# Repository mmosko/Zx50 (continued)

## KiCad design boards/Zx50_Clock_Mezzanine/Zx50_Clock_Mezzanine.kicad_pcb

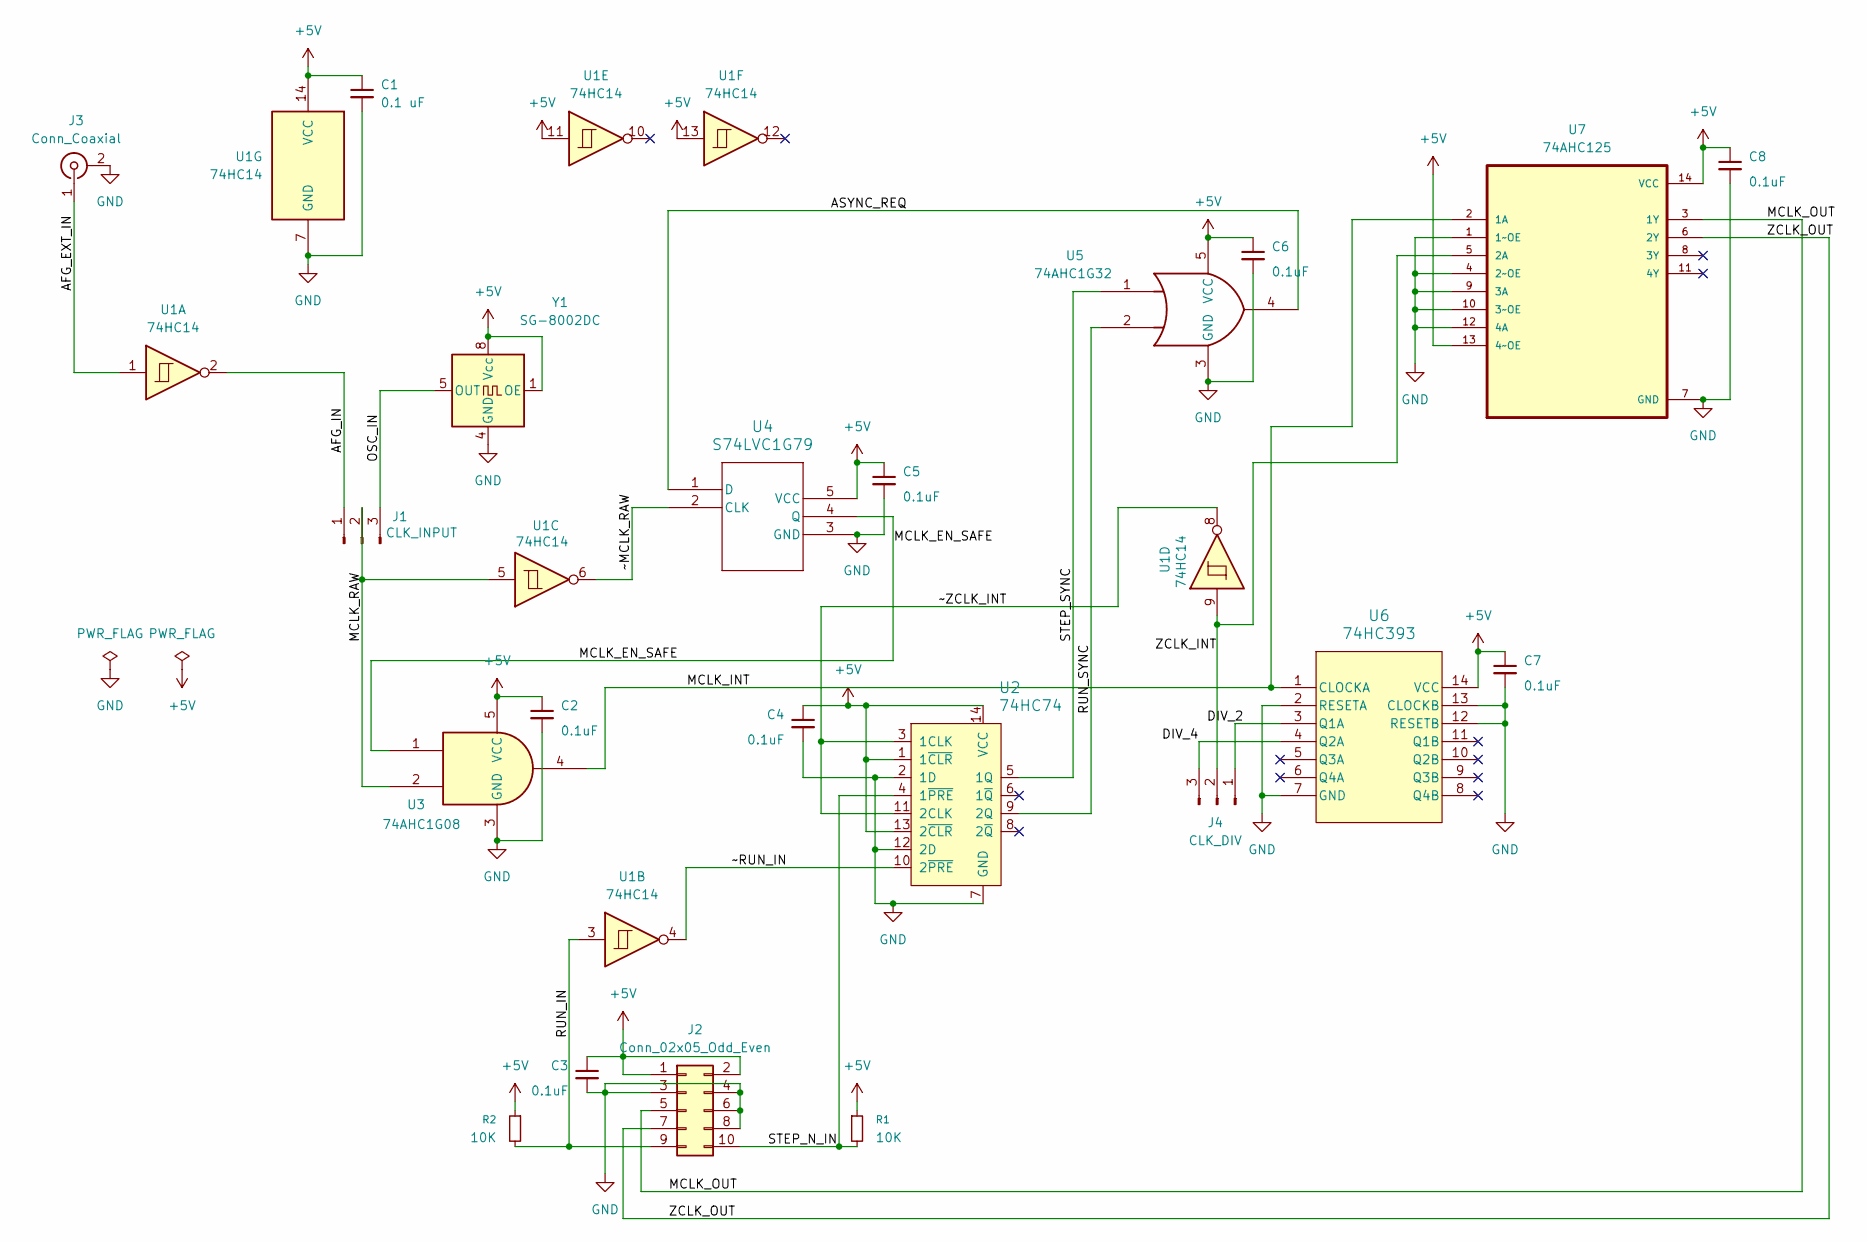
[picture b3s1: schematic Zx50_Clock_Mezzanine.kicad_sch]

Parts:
C1: 0.1 uF; C_0805_2012Metric_Pad1.18x1.45mm_HandSolder; DigiKey_PN 311-1140-1-ND
C2, C3, C4, C5, C6, C7, C8: 0.1uF; C_0805_2012Metric_Pad1.18x1.45mm_HandSolder; DigiKey_PN 311-1140-1-ND
J1: CLK_INPUT; PinHeader_1x03_P2.54mm_Vertical; DigiKey_PN 732-5316-ND
J2: Conn_02x05_Odd_Even; PinHeader_2x05_P2.54mm_Vertical; DigiKey_PN 2057-PH2RA-10-UA-ND
J3: Conn_Coaxial; BNC_Amphenol_B6252HB-NPP3G-50_Horizontal; DigiKey_PN ARF1178-ND
J4: CLK_DIV; PinHeader_1x03_P2.54mm_Vertical; DigiKey_PN 732-5316-ND
R1, R2: 10K; R_0805_2012Metric_Pad1.20x1.40mm_HandSolder; DigiKey_PN 311-10.0KCRCT-ND
U1: 74HC14; SOIC-14_3.9x8.7mm_P1.27mm; DigiKey_PN MC74HC14ADR2GOSCT-ND
U2: 74HC74; SOIC-14_3.9x8.7mm_P1.27mm; MPN SN74HC74N; Digi-Key_PN 296-1602-5-ND
U3: 74AHC1G08; SOT-23-5_HandSoldering; DigiKey_PN 296-1091-1-ND
U4: S74LVC1G79; SOT-23-5_HandSoldering; DigiKey_PN 296-9849-1-ND
U5: 74AHC1G32; SOT-23-5_HandSoldering; DigiKey_PN 296-1093-1-ND
U6: 74HC393; SOIC-14_3.9x8.7mm_P1.27mm; DigiKey_PN 296-8317-5-ND
U7: 74AHC125; SOIC-14_3.9x8.7mm_P1.27mm; DigiKey_PN 296-4530-1-ND
Y1: SG-8002DC; DIP-8_W7.62mm_Socket; DigiKey_PN 17-2485264-1-ND

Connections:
+5V: C1.1, C2.1, C3.1, C4.1, C5.1, C6.1, C7.1, C8.1, J2.1, J2.2, R1.1, R2.1, U1.11, U1.13, U1.14 (VCC), U2.1 (1~CLR), U2.13 (2~CLR), U2.14 (VCC), U3.5 (VCC), U4.5 (VCC), U5.5 (VCC), U6.14 (VCC), U7.13 (4~OE), U7.14 (VCC), Y1.1 (OE), Y1.8 (Vcc)
/AFG_EXT_IN: J3.1 (In), U1.1
/AFG_IN: J1.1, U1.2
/ASYNC_REQ: U4.1 (D), U5.4
/DIV_2: J4.1, U6.3 (Q1A)
/DIV_4: J4.3, U6.4 (Q2A)
/MCLK_EN_SAFE: U3.1, U4.4 (Q)
/MCLK_INT: U3.4, U6.1 (CLOCKA), U7.2 (1A)
/MCLK_OUT: J2.5, U7.3 (1Y)
/MCLK_RAW: J1.2, U1.5, U3.2
/OSC_IN: J1.3, Y1.5 (OUT)
/RUN_IN: J2.9, R2.2, U1.3
/RUN_SYNC: U2.9 (2Q), U5.2
/STEP_N_IN: J2.10, R1.2, U2.4 (1~PRE)
/STEP_SYNC: U2.5 (1Q), U5.1
/ZCLK_INT: J4.2, U1.9, U7.5 (2A)
/ZCLK_OUT: J2.7, U7.6 (2Y)
/~MCLK_RAW: U1.6, U4.2 (CLK)
/~RUN_IN: U1.4, U2.10 (2~PRE)
/~ZCLK_INT: U1.8, U2.3 (1CLK), U2.11 (2CLK)
GND: C1.2, C2.2, C3.2, C4.2, C5.2, C6.2, C7.2, C8.2, J2.3, J2.4, J2.6, J2.8, J3.2 (Ext), U1.7 (GND), U2.2 (1D), U2.7 (GND), U2.12 (2D), U3.3 (GND), U4.3 (GND), U5.3 (GND), U6.2 (RESETA), U6.7 (GND), U6.12 (RESETB), U6.13 (CLOCKB), U7.1 (1~OE), U7.4 (2~OE), U7.7 (GND), U7.9 (3A), U7.10 (3~OE), U7.12 (4A), Y1.4 (GND)

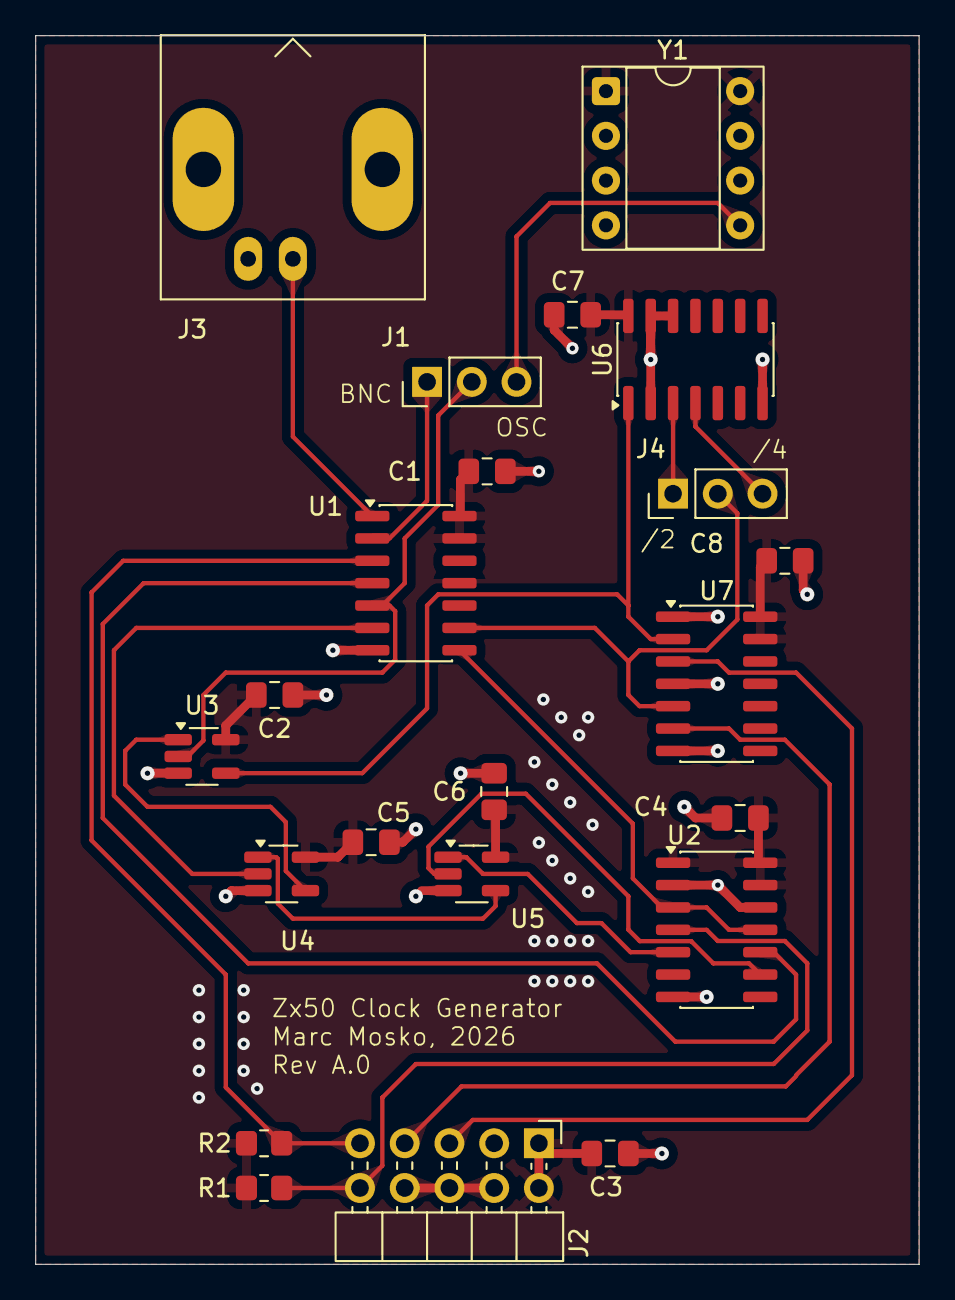
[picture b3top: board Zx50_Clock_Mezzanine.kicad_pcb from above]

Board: 2 copper layers, 50.2 x 69.8 mm, 22 parts (0 on the bottom side), 21 nets.

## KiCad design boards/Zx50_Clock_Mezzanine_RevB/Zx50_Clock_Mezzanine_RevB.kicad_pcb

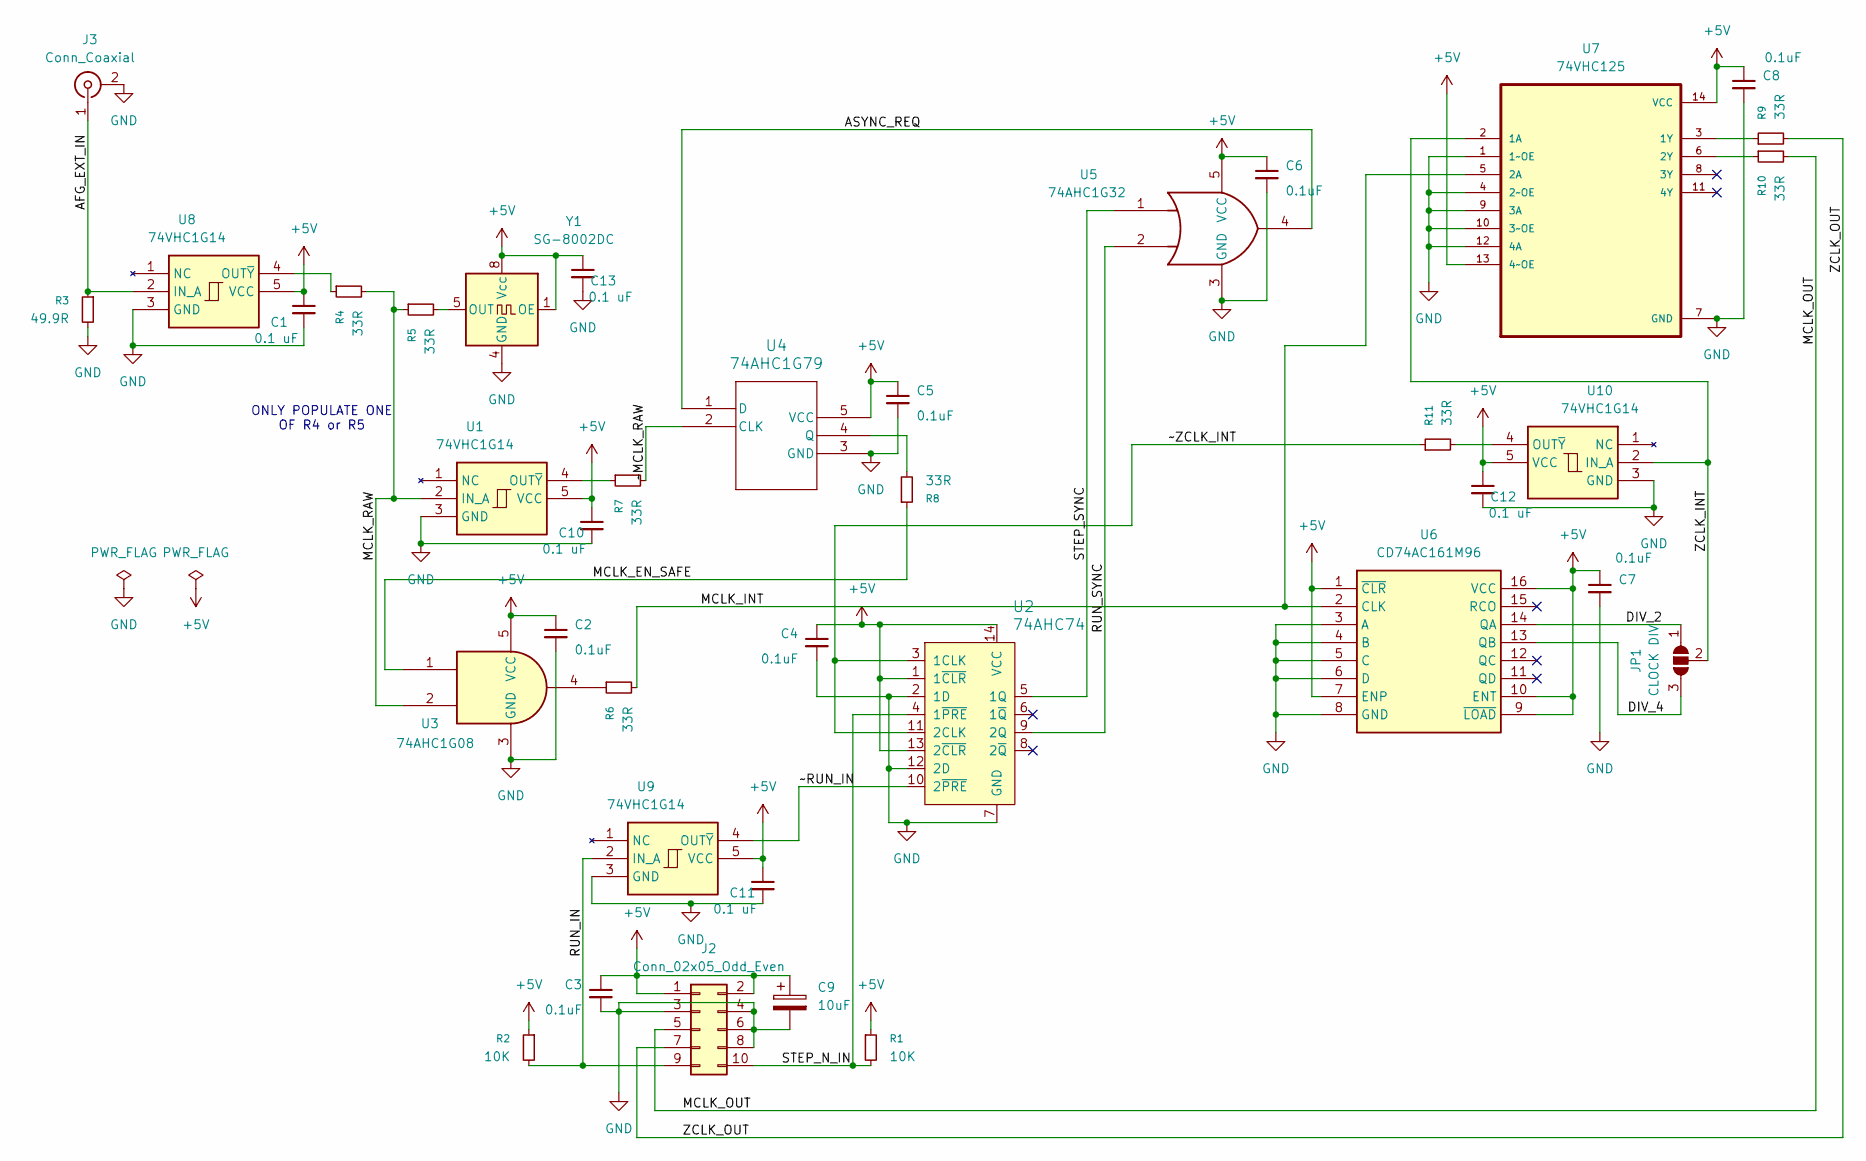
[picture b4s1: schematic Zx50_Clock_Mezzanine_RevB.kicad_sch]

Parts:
C1, C10, C11, C12, C13: 0.1 uF; C_0805_2012Metric_Pad1.18x1.45mm_HandSolder; DigiKey_PN 311-1140-1-ND
C2, C3, C4, C5, C6, C7, C8: 0.1uF; C_0805_2012Metric_Pad1.18x1.45mm_HandSolder; DigiKey_PN 311-1140-1-ND
C9: 10uF; CP_Radial_Tantal_D5.0mm_P2.50mm; Mouser_PN 80-T350E106K025; DigiKey_PN 399-1418-ND
J2: Conn_02x05_Odd_Even; PinHeader_2x05_P2.54mm_Vertical; DigiKey_PN 2057-PH2RA-10-UA-ND
J3: Conn_Coaxial; BNC_Amphenol_B6252HB-NPP3G-50_Horizontal; DigiKey_PN ARF1178-ND
JP1: CLOCK DIV; SolderJumper-3_P1.3mm_Open_RoundedPad1.0x1.5mm
R1, R2: 10K; R_0805_2012Metric_Pad1.20x1.40mm_HandSolder; DigiKey_PN 311-10.0KCRCT-ND
R3: 49.9R; R_0805_2012Metric_Pad1.20x1.40mm_HandSolder; DigiKey_PN 311-49.9KCRCT-ND
R4, R5, R6, R7, R8, R9, R10, R11: 33R; R_0805_2012Metric_Pad1.20x1.40mm_HandSolder; DigiKey_PN 311-33.0CRCT-ND
U1, U8, U9, U10: 74VHC1G14; SOT-23-5_HandSoldering; Mouser Part Number 863-MC74VHC1G14DBVTG
U2: 74AHC74; SOIC-14_3.9x8.7mm_P1.27mm; MPN SN74AHC74DR; Digi-Key_PN 296-1105-1-ND
U3: 74AHC1G08; SOT-23-5_HandSoldering; DigiKey_PN 296-1091-1-ND
U4: 74AHC1G79; SOT-23-5_HandSoldering; DigiKey_PN 1727-6765-1-ND
U5: 74AHC1G32; SOT-23-5_HandSoldering; DigiKey_PN 296-1093-1-ND
U6: CD74AC161M96; SOIC-16_3.9x9.9mm_P1.27mm; Mouser Part Number 595-CD74AC161M96
U7: 74VHC125; SOIC-14_3.9x8.7mm_P1.27mm; DigiKey_PN MC74VHC125DR2GOSCT-ND
Y1: SG-8002DC; DIP-8_W7.62mm_Socket; DigiKey_PN 17-2485264-1-ND

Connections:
+5V: C1.1, C2.1, C3.1, C4.1, C5.1, C6.1, C7.1, C8.1, C9.1, C10.1, C11.1, C12.1, C13.1, J2.1, J2.2, R1.1, R2.1, U1.5 (VCC), U2.1 (1~CLR), U2.13 (2~CLR), U2.14 (VCC), U3.5 (VCC), U4.5 (VCC), U5.5 (VCC), U6.1 (~CLR), U6.7 (ENP), U6.9 (~LOAD), U6.10 (ENT), U6.16 (VCC), U7.13 (4~OE), U7.14 (VCC), U8.5 (VCC), U9.5 (VCC), U10.5 (VCC), Y1.1 (OE), Y1.8 (Vcc)
/AFG_EXT_IN: J3.1 (In), R3.1, U8.2 (IN_A)
/ASYNC_REQ: U4.1 (D), U5.4
/DIV_2: JP1.1 (A), U6.14 (QA)
/DIV_4: JP1.3 (B), U6.13 (QB)
/MCLK_EN_SAFE: R8.1, U3.1
/MCLK_INT: R6.2, U6.2 (CLK), U7.5 (2A)
/MCLK_OUT: J2.5, R10.2
/MCLK_RAW: R4.2, R5.1, U1.2 (IN_A), U3.2
/RUN_IN: J2.9, R2.2, U9.2 (IN_A)
/RUN_SYNC: U2.9 (2Q), U5.2
/STEP_N_IN: J2.10, R1.2, U2.4 (1~PRE)
/STEP_SYNC: U2.5 (1Q), U5.1
/ZCLK_INT: JP1.2 (C), U7.2 (1A), U10.2 (IN_A)
/ZCLK_OUT: J2.7, R9.2
/~MCLK_RAW: R7.2, U4.2 (CLK)
/~RUN_IN: U2.10 (2~PRE), U9.4 (OUT~Y)
/~ZCLK_INT: R11.1, U2.3 (1CLK), U2.11 (2CLK)
GND: C1.2, C2.2, C3.2, C4.2, C5.2, C6.2, C7.2, C8.2, C9.2, C10.2, C11.2, C12.2, C13.2, J2.3, J2.4, J2.6, J2.8, J3.2 (Ext), R3.2, U1.3 (GND), U2.2 (1D), U2.7 (GND), U2.12 (2D), U3.3 (GND), U4.3 (GND), U5.3 (GND), U6.3 (A), U6.4 (B), U6.5 (C), U6.6 (D), U6.8 (GND), U7.1 (1~OE), U7.4 (2~OE), U7.7 (GND), U7.9 (3A), U7.10 (3~OE), U7.12 (4A), U8.3 (GND), U9.3 (GND), U10.3 (GND), Y1.4 (GND)
unnamed: R6.1, U3.4
unnamed: R7.1, U1.4 (OUT~Y)
unnamed: R8.2, U4.4 (Q)
unnamed: R9.1, U7.3 (1Y)
unnamed: R10.1, U7.6 (2Y)
unnamed: R4.1, U8.4 (OUT~Y)
unnamed: R11.2, U10.4 (OUT~Y)
unnamed: R5.2, Y1.5 (OUT)

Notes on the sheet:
ONLY POPULATE ONE OF R4 or R5

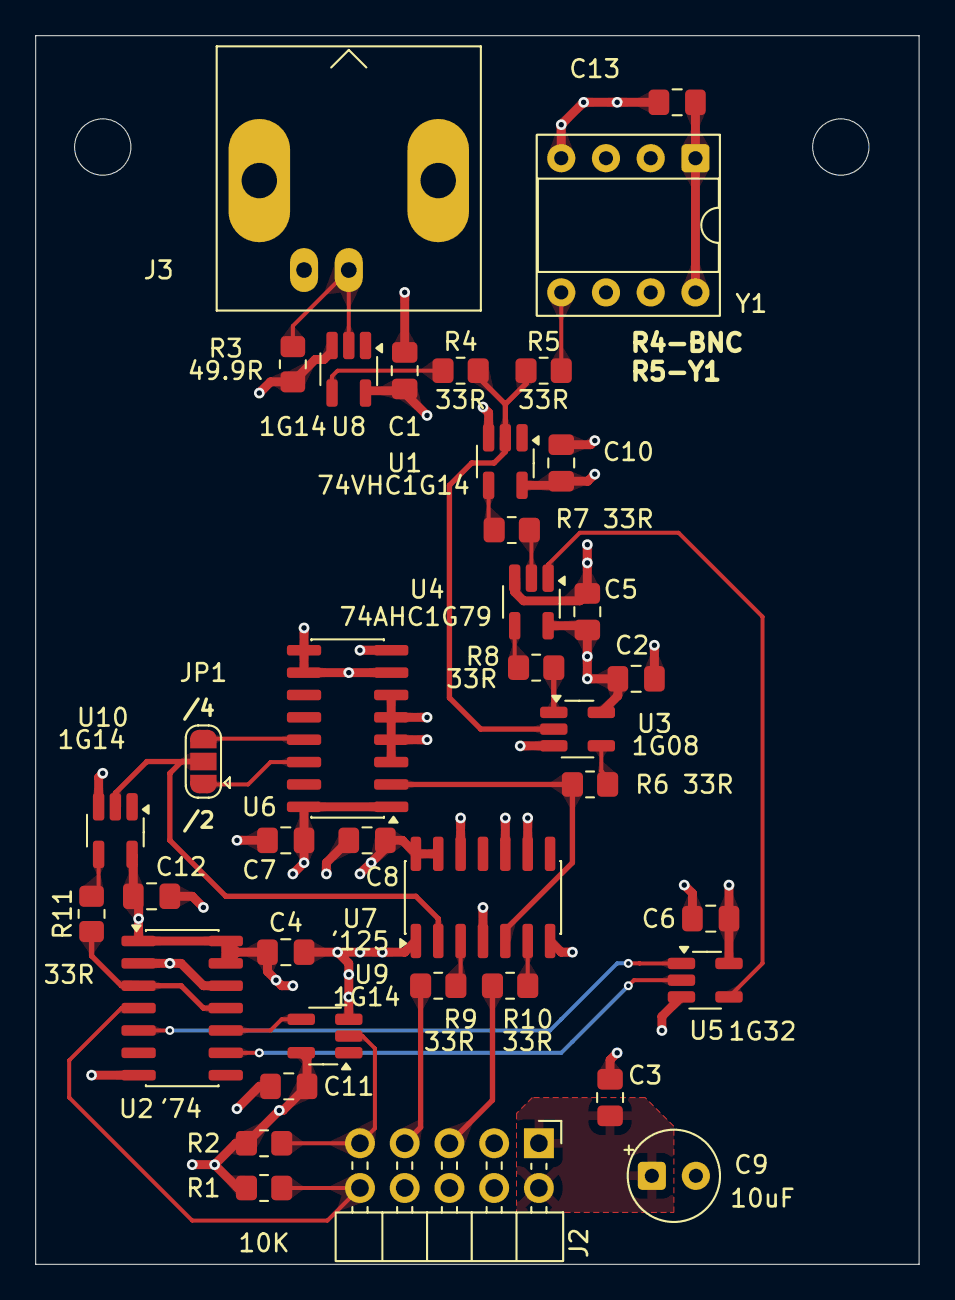
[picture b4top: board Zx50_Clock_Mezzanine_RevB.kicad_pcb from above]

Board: 4 copper layers, 50.2 x 69.8 mm, 38 parts (0 on the bottom side), 27 nets.

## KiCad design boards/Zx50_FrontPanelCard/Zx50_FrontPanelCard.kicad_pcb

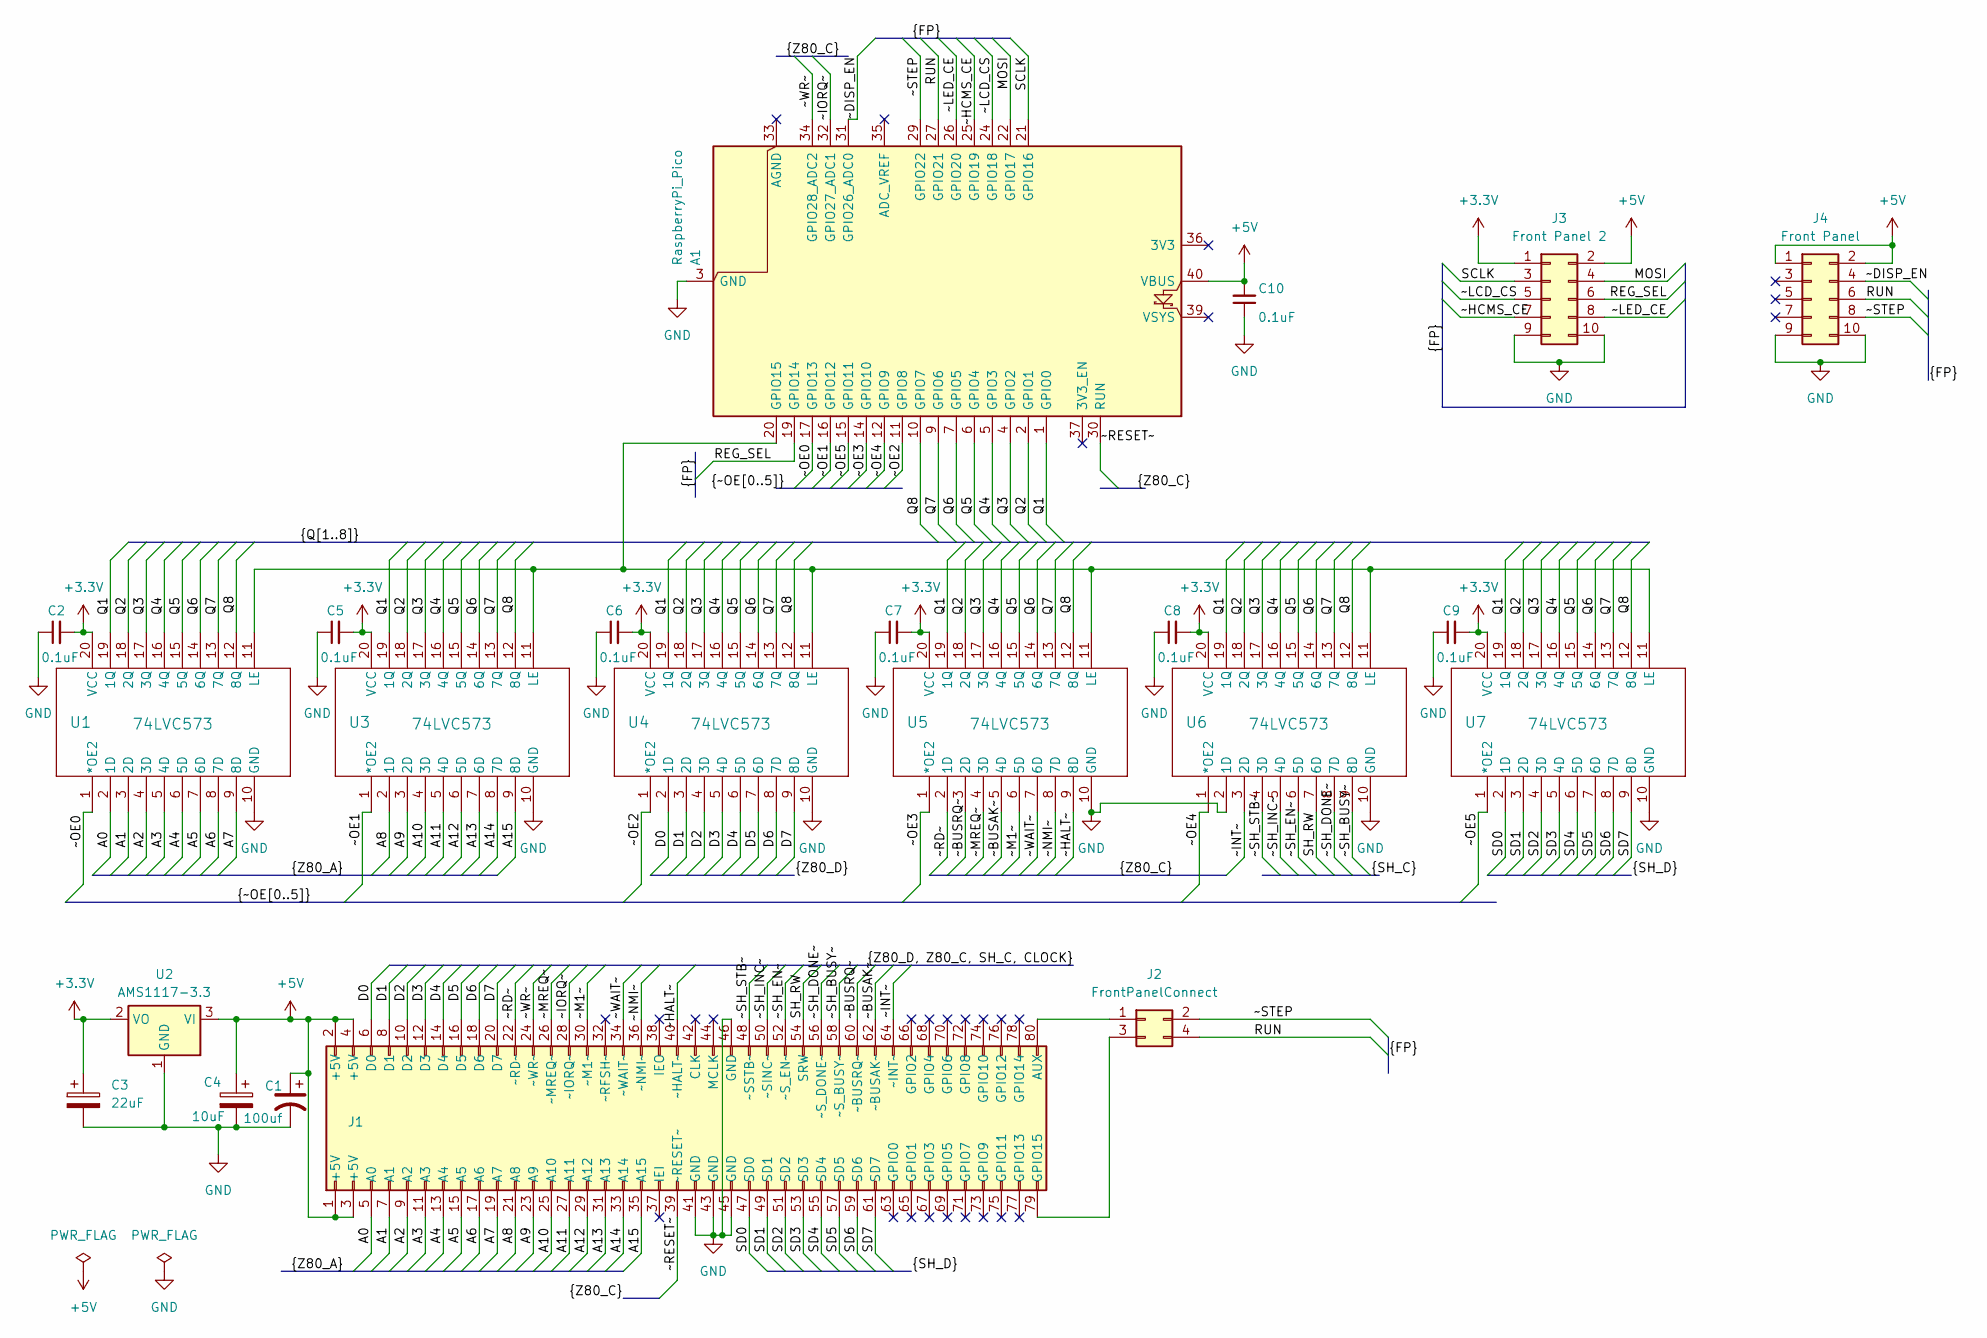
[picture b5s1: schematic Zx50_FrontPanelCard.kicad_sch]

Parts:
A1: RaspberryPi_Pico; RaspberryPi_Pico_Common_Unspecified; Mouser_PN 358-SC1634; Digi-Key_PN SC1634
C1: 100uf; CP_Radial_D10.0mm_P5.00mm
C2, C5, C6, C7, C8, C9, C10: 0.1uF; C_Disc_D5.0mm_W2.5mm_P5.00mm; DigiKey_PN BC1101CT-ND
C3: 22uF; CP_Radial_Tantal_D5.0mm_P2.50mm; Mouser_PN 80-T350E226K010AT; DigiKey_PN 399-1418-ND
C4: 10uF; CP_Radial_Tantal_D5.0mm_P2.50mm; Mouser_PN 80-T350E106K025; DigiKey_PN 399-1418-ND
J1: Zx50_EdgeConnector; PinSocket_2x40_P2.54mm_Vertical_Oval; Mouser_PN 737-PH2RA-80-UA; Digi-Key_PN 2057-PH2RA-80-UA-ND
J2: FrontPanelConnect; PinSocket_2x02_P2.54mm_Vertical; DigiKey_PN S1012E-02-ND
J3: Front Panel 2; IDC-Header_2x05_P2.54mm_Horizontal_Edge; Mouser_PN 710-61201022921; DigiKey_PN 732-2098-ND
J4: Front Panel; IDC-Header_2x05_P2.54mm_Horizontal_Edge; Mouser_PN 710-61201022921; DigiKey_PN 732-2098-ND
U1, U3, U4, U5, U6, U7: 74LVC573; SOIC-20W_7.5x12.8mm_P1.27mm; Mouser_PN 595-SN74LVC573ADW; DigiKey_PN 296-8527-5-ND
U2: AMS1117-3.3; SOT-223-3_TabPin2; Mouser_PN 926-LM1117MPX3.3NOPB

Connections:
+3.3V: C2.2, C3.1, C5.2, C6.2, C7.2, C8.2, C9.2, J3.1, U1.20 (VCC), U2.2 (VO), U3.20 (VCC), U4.20 (VCC), U5.20 (VCC), U6.20 (VCC), U7.20 (VCC)
+5V: A1.40 (VBUS), C1.1, C4.1, C10.2, J1.1 (+5V), J1.2 (+5V), J1.3 (+5V), J1.4 (+5V), J3.2, J4.1, J4.2, U2.3 (VI)
/A0: J1.5 (A0), U1.2 (1D)
/A1: J1.7 (A1), U1.3 (2D)
/A2: J1.9 (A2), U1.4 (3D)
/A3: J1.11 (A3), U1.5 (4D)
/A4: J1.13 (A4), U1.6 (5D)
/A5: J1.15 (A5), U1.7 (6D)
/A6: J1.17 (A6), U1.8 (7D)
/A7: J1.19 (A7), U1.9 (8D)
/A8: J1.21 (A8), U3.2 (1D)
/A9: J1.23 (A9), U3.3 (2D)
/A10: J1.25 (A10), U3.4 (3D)
/A11: J1.27 (A11), U3.5 (4D)
/A12: J1.29 (A12), U3.6 (5D)
/A13: J1.31 (A13), U3.7 (6D)
/A14: J1.33 (A14), U3.8 (7D)
/A15: J1.35 (A15), U3.9 (8D)
/D0: J1.6 (D0), U4.2 (1D)
/D1: J1.8 (D1), U4.3 (2D)
/D2: J1.10 (D2), U4.4 (3D)
/D3: J1.12 (D3), U4.5 (4D)
/D4: J1.14 (D4), U4.6 (5D)
/D5: J1.16 (D5), U4.7 (6D)
/D6: J1.18 (D6), U4.8 (7D)
/D7: J1.20 (D7), U4.9 (8D)
/MOSI: A1.22 (GPIO17), J3.4
/Q1: A1.1 (GPIO0), U1.19 (1Q), U3.19 (1Q), U4.19 (1Q), U5.19 (1Q), U6.19 (1Q), U7.19 (1Q)
/Q2: A1.2 (GPIO1), U1.18 (2Q), U3.18 (2Q), U4.18 (2Q), U5.18 (2Q), U6.18 (2Q), U7.18 (2Q)
/Q3: A1.4 (GPIO2), U1.17 (3Q), U3.17 (3Q), U4.17 (3Q), U5.17 (3Q), U6.17 (3Q), U7.17 (3Q)
/Q4: A1.5 (GPIO3), U1.16 (4Q), U3.16 (4Q), U4.16 (4Q), U5.16 (4Q), U6.16 (4Q), U7.16 (4Q)
/Q5: A1.6 (GPIO4), U1.15 (5Q), U3.15 (5Q), U4.15 (5Q), U5.15 (5Q), U6.15 (5Q), U7.15 (5Q)
/Q6: A1.7 (GPIO5), U1.14 (6Q), U3.14 (6Q), U4.14 (6Q), U5.14 (6Q), U6.14 (6Q), U7.14 (6Q)
/Q7: A1.9 (GPIO6), U1.13 (7Q), U3.13 (7Q), U4.13 (7Q), U5.13 (7Q), U6.13 (7Q), U7.13 (7Q)
/Q8: A1.10 (GPIO7), U1.12 (8Q), U3.12 (8Q), U4.12 (8Q), U5.12 (8Q), U6.12 (8Q), U7.12 (8Q)
/REG_SEL: A1.19 (GPIO14), J3.6
/RUN: A1.27 (GPIO21), J2.4, J4.6
/SCLK: A1.21 (GPIO16), J3.3
/SD0: J1.47 (SD0), U7.2 (1D)
/SD1: J1.49 (SD1), U7.3 (2D)
/SD2: J1.51 (SD2), U7.4 (3D)
/SD3: J1.53 (SD3), U7.5 (4D)
/SD4: J1.55 (SD4), U7.6 (5D)
/SD5: J1.57 (SD5), U7.7 (6D)
/SD6: J1.59 (SD6), U7.8 (7D)
/SD7: J1.61 (SD7), U7.9 (8D)
/SH_RW: J1.54 (SRW), U6.7 (6D)
/~BUSAK~: J1.62 (~BUSAK~), U5.5 (4D)
/~BUSRQ~: J1.60 (~BUSRQ~), U5.3 (2D)
/~DISP_EN: A1.31 (GPIO26_ADC0), J4.4
/~HALT~: J1.40 (~HALT~), U5.9 (8D)
/~HCMS_CE: A1.25 (GPIO19), J3.7
/~INT~: J1.64 (~INT~), U6.3 (2D)
/~IORQ~: A1.32 (GPIO27_ADC1), J1.28 (~IORQ~)
/~LCD_CS: A1.24 (GPIO18), J3.5
/~LED_CE: A1.26 (GPIO20), J3.8
/~M1~: J1.30 (~M1~), U5.6 (5D)
/~MREQ~: J1.26 (~MREQ~), U5.4 (3D)
/~NMI~: J1.36 (~NMI~), U5.8 (7D)
/~OE0: A1.17 (GPIO13), U1.1 (*OE2)
/~OE1: A1.16 (GPIO12), U3.1 (*OE2)
/~OE2: A1.11 (GPIO8), U4.1 (*OE2)
/~OE3: A1.14 (GPIO10), U5.1 (*OE2)
/~OE4: A1.12 (GPIO9), U6.1 (*OE2)
/~OE5: A1.15 (GPIO11), U7.1 (*OE2)
/~RD~: J1.22 (~RD~), U5.2 (1D)
/~RESET~: A1.30 (RUN), J1.39 (~RESET~)
/~SH_BUSY~: J1.58 (~S_BUSY~), U6.9 (8D)
/~SH_DONE~: J1.56 (~S_DONE~), U6.8 (7D)
/~SH_EN~: J1.52 (~S_EN~), U6.6 (5D)
/~SH_INC~: J1.50 (~SINC~), U6.5 (4D)
/~SH_STB~: J1.48 (~SSTB~), U6.4 (3D)
/~STEP: A1.29 (GPIO22), J2.2, J4.8
/~WAIT~: J1.34 (~WAIT~), U5.7 (6D)
/~WR~: A1.34 (GPIO28_ADC2), J1.24 (~WR~)
GND: A1.3 (GND), A1.8 (GND), A1.13 (GND), A1.18 (GND), A1.23 (GND), A1.28 (GND), A1.38 (GND), C1.2, C2.1, C3.2, C4.2, C5.1, C6.1, C7.1, C8.1, C9.1, C10.1, J1.41 (GND), J1.43 (GND), J1.45 (GND), J1.46 (GND), J3.9, J3.10, J4.9, J4.10, U1.10 (GND), U2.1 (GND), U3.10 (GND), U4.10 (GND), U5.10 (GND), U6.2 (1D), U6.10 (GND), U7.10 (GND)
unnamed: A1.20 (GPIO15), U1.11 (LE), U3.11 (LE), U4.11 (LE), U5.11 (LE), U6.11 (LE), U7.11 (LE)
unnamed: J1.80 (AUX), J2.1
unnamed: J1.79 (GPIO15), J2.3

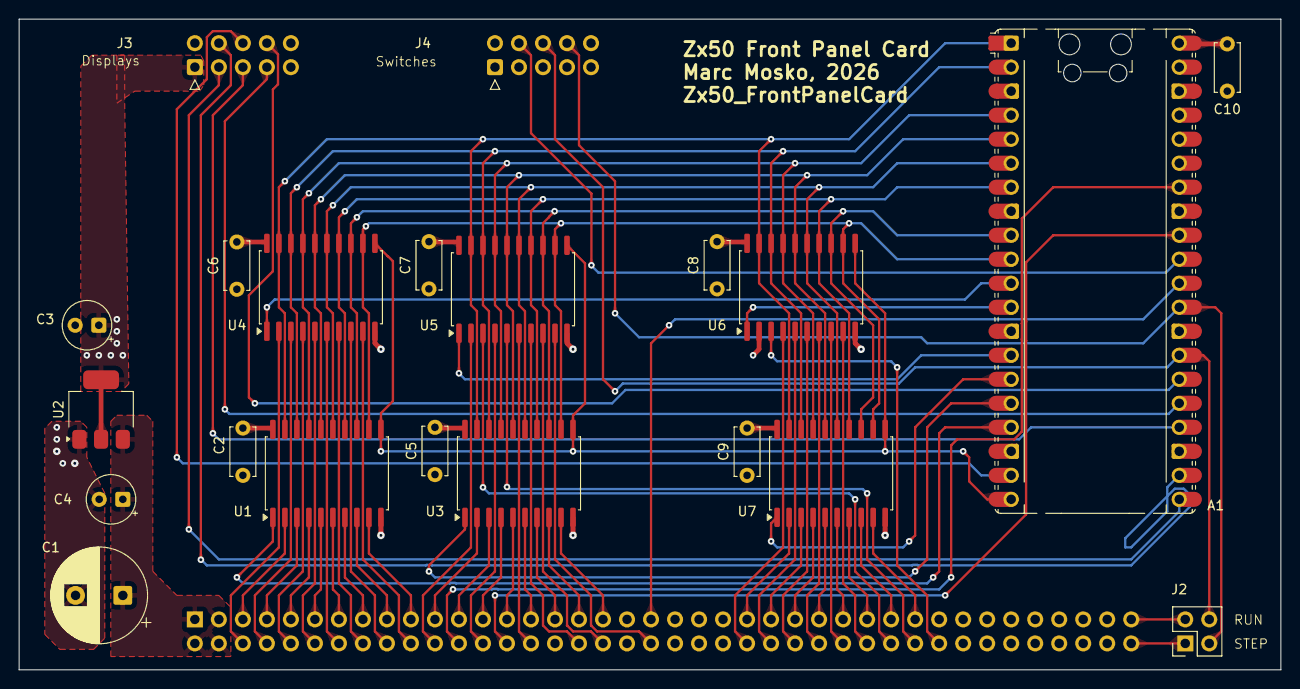
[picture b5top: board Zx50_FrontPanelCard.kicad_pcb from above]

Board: 4 copper layers, 133.5 x 68.8 mm, 22 parts (1 on the bottom side), 79 nets.
